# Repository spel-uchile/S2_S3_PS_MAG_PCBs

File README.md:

# S2_S3_PS_MAG_PCBs
A summary of the different MAG derived PCBs used in SUCHAI 2, SUCHAI 3 and Plansat Satellites

## Folder Content

- CADs: CAD files of some PCBs
- Grafeno V2: KiCAD version of Graphene PCB (for debugging)
- mini_sensor: Magnetometer PCB sensor implementation for testing
- PAD: Panel A Cubesat with holes for Langmuir Probe voltage regulator (used as dummy Panel A)
- Panel A E S2: External Panel A Suchai-2. Includes the Magnetometer socket and holes to place the Shielded Langmuir Probe Electronic PCB.
- Panel A E S2 - Plansat: External Panel A Plansat. Includes the Magnetometer socket.
- Panel A E S3: External Panel A Suchai-3. Includes the Magnetometer socket and holes to place the Langmuir Probe Sensor (Not Used).
- Panel A I S2: Internal Panel A Suchai-2. Includes the pines to place the Langmuir Probe voltage Regulator and a hole to introduce the Langmuir Probe PCB Shield beyond the PCB.
- Panel A I S3: Internal Panel A Suchai-3. Includes the pines to place the Langmuir Probe voltage Regulator and a hole to introduce the Langmuir Probe PCB Shield beyond the PCB (Not Used).
- Panel B E S2: External Panel B Suchai-2. Includes the Magnetometer socket and holes to place the Shielded Langmuir Probe Electronic PCB (Not used).
- Panel B E S3: External Panel B Suchai-3. Includes the Magnetometer socket and holes to place the Langmuir Probe Sensor. It also includes a hole for a Particle counter sensor.
- Panel B E S3 - Plansat: External Panel B Plansat. Includes the Magnetometer socket.
- Panel B I S2: Internal Panel B Suchai-2. Includes holes to place the Langmuir Probe Wire (PCB-Sensor) and the Raspberry Pi Camera (Not Used).
- Panel B I S3: Internal Panel B Suchai-3. Includes holes to place the Langmuir Probe Wire (PCB-Sensor), GPS, and the Raspberry Pi Camera.
- Panel B I S3 PC: Internal Panel B Suchai-3. Includes a Particle Counter Circuit Implementation, holes to place the Langmuir Probe Wire (PCB-Sensor), GPS, and the Raspberry Pi Camera.
- Panel Test: PCB to check the achievement of the maximum limits for lateral panels of the Satellite.
- PDB: Dummy Panel B.
- PC: KiCAD version of Particle Counter Prototype Circuit.
- PC104: Magnetometer PCB (MAG) PC104 PCB, Version 1 (Not used).
- PC104 - Plansat: Magnetometer PCB (MAG) PC104 PCB, Plansat Version.
- PC104_V2: Magnetometer PCB (MAG+) PC104 PCB, Version 2 (Used in Suchai-2).
- PC104_V3: Magnetometer PCB (Super MAG+) PC104 PCB, Version 3 (Used in Suchai-3).
- PC104_V3P2: Magnetometer PCB (Super MAG+) PC104 PCB, Version 3 (Added MCP3204 as AOA ADC).
- PC104 main: Compilation of the PC104 and panels used in the project (Version 1).
- PCD: Dummy Panel C.

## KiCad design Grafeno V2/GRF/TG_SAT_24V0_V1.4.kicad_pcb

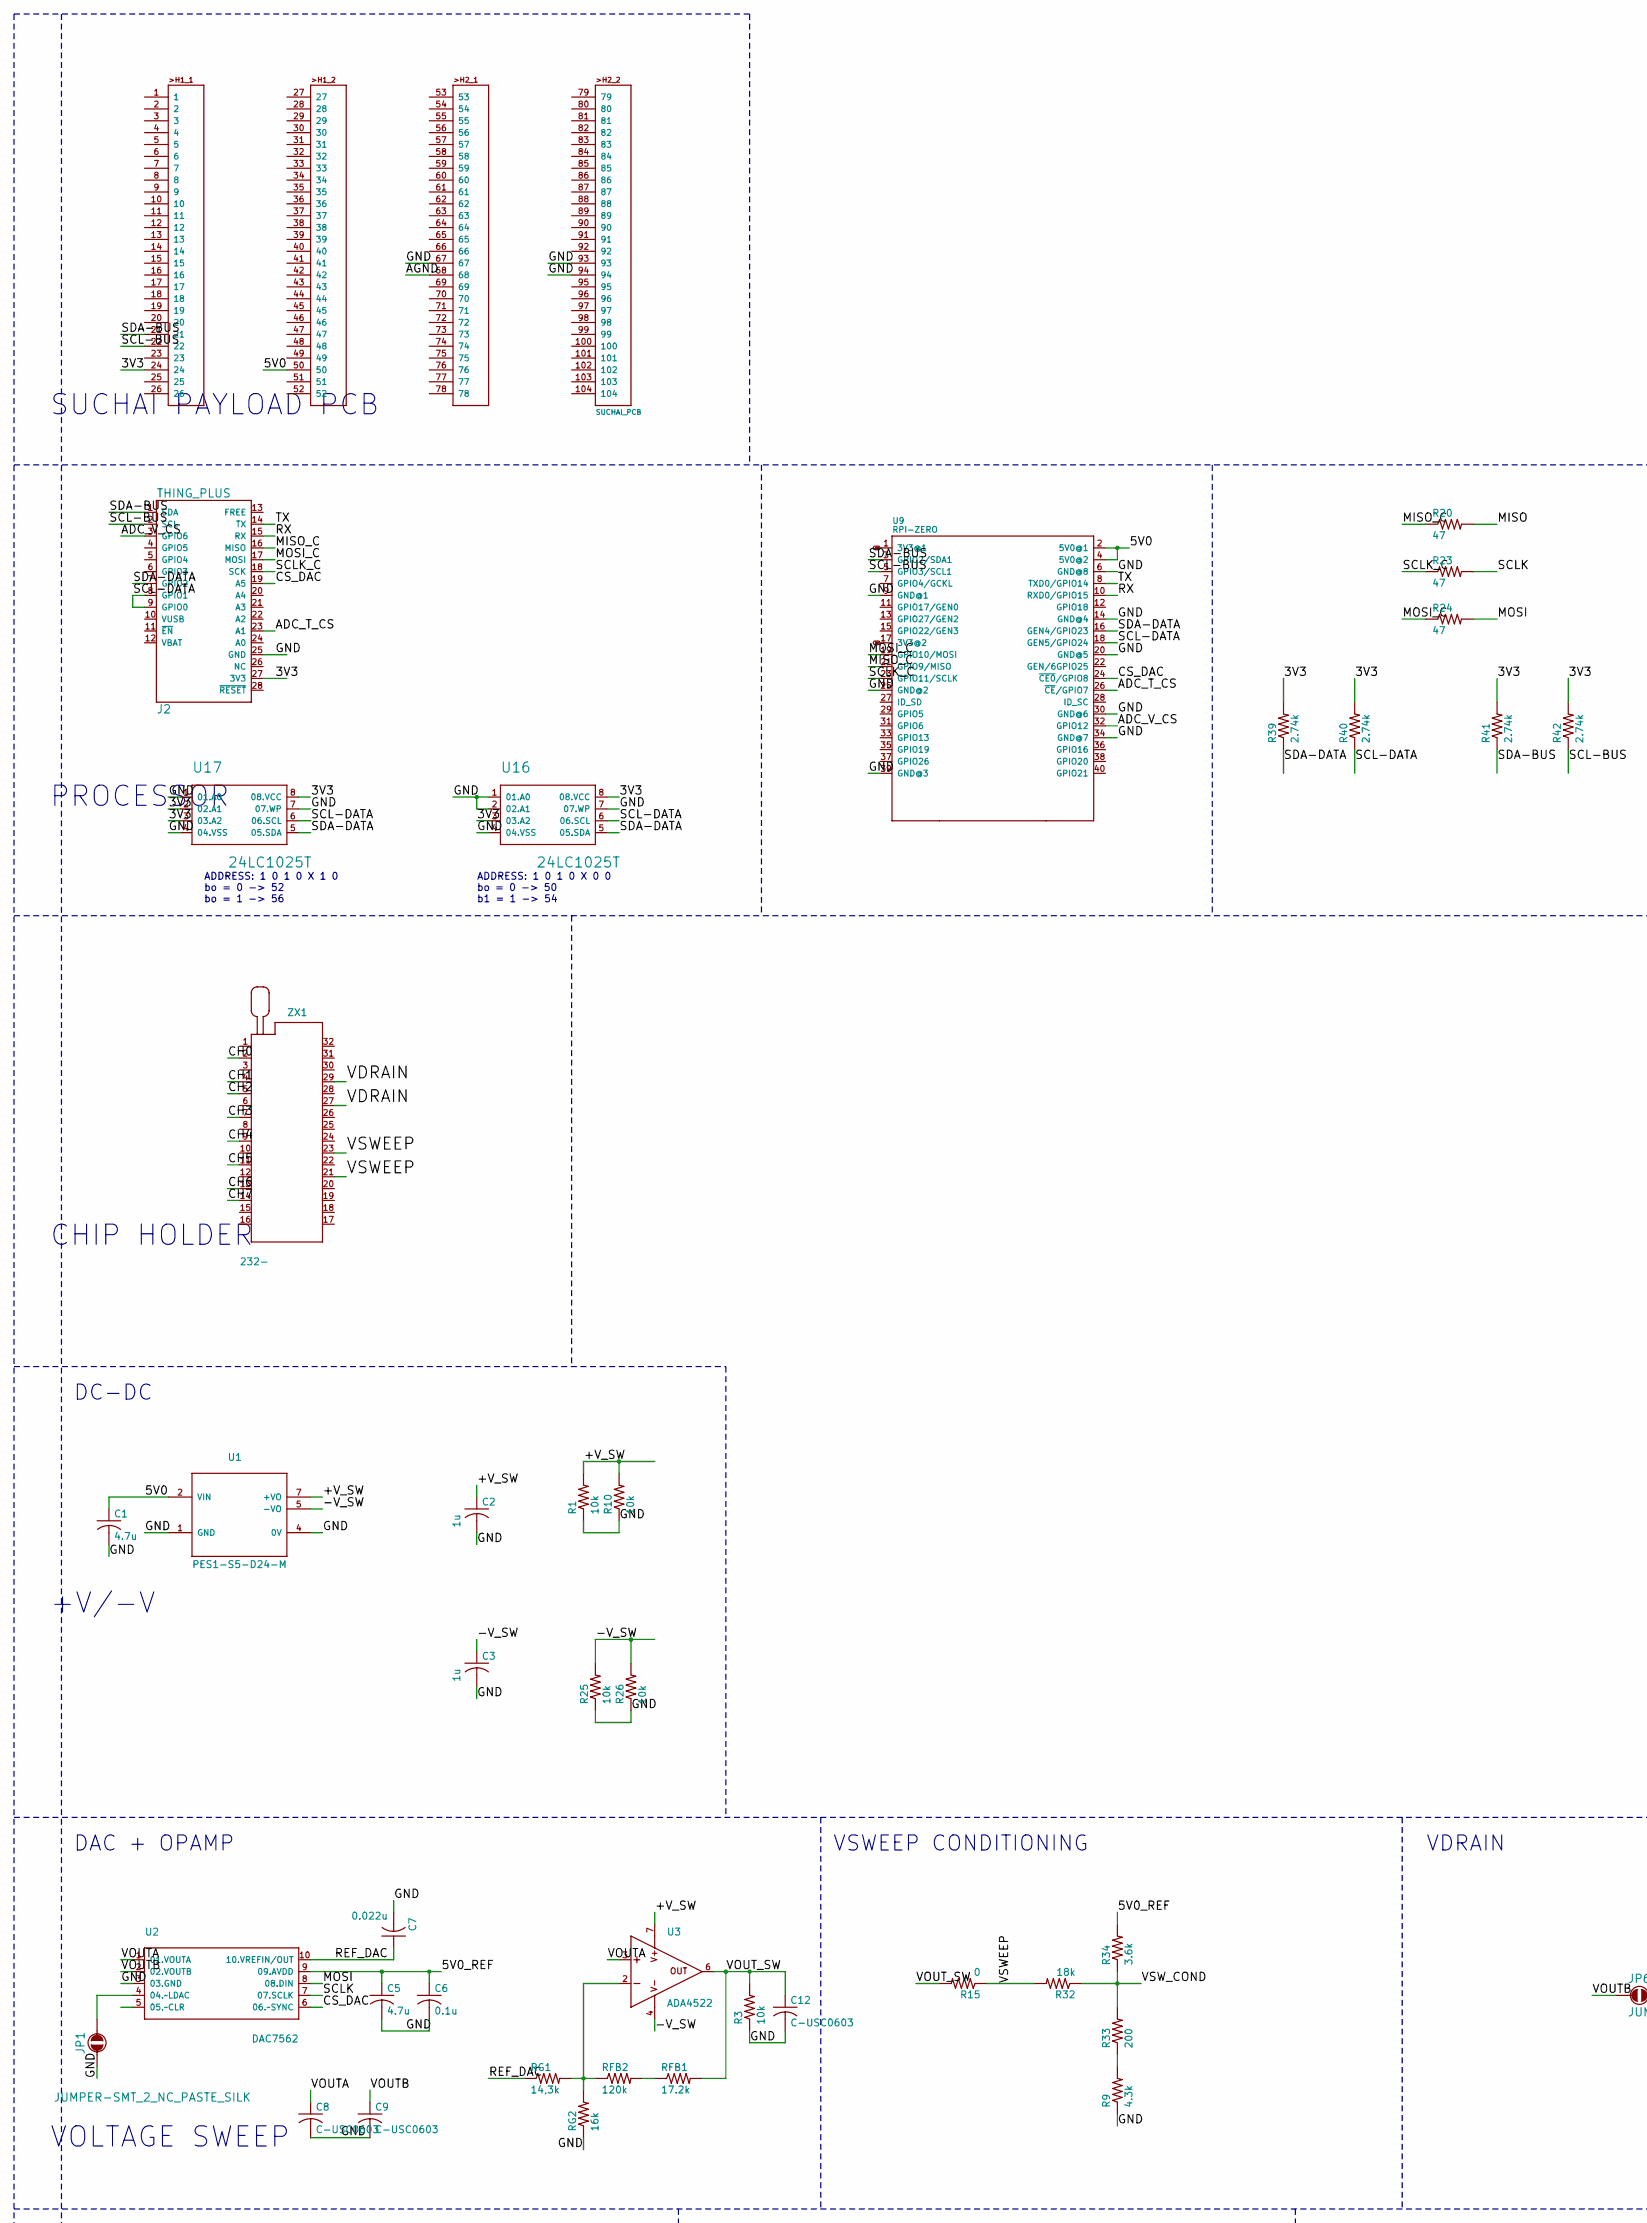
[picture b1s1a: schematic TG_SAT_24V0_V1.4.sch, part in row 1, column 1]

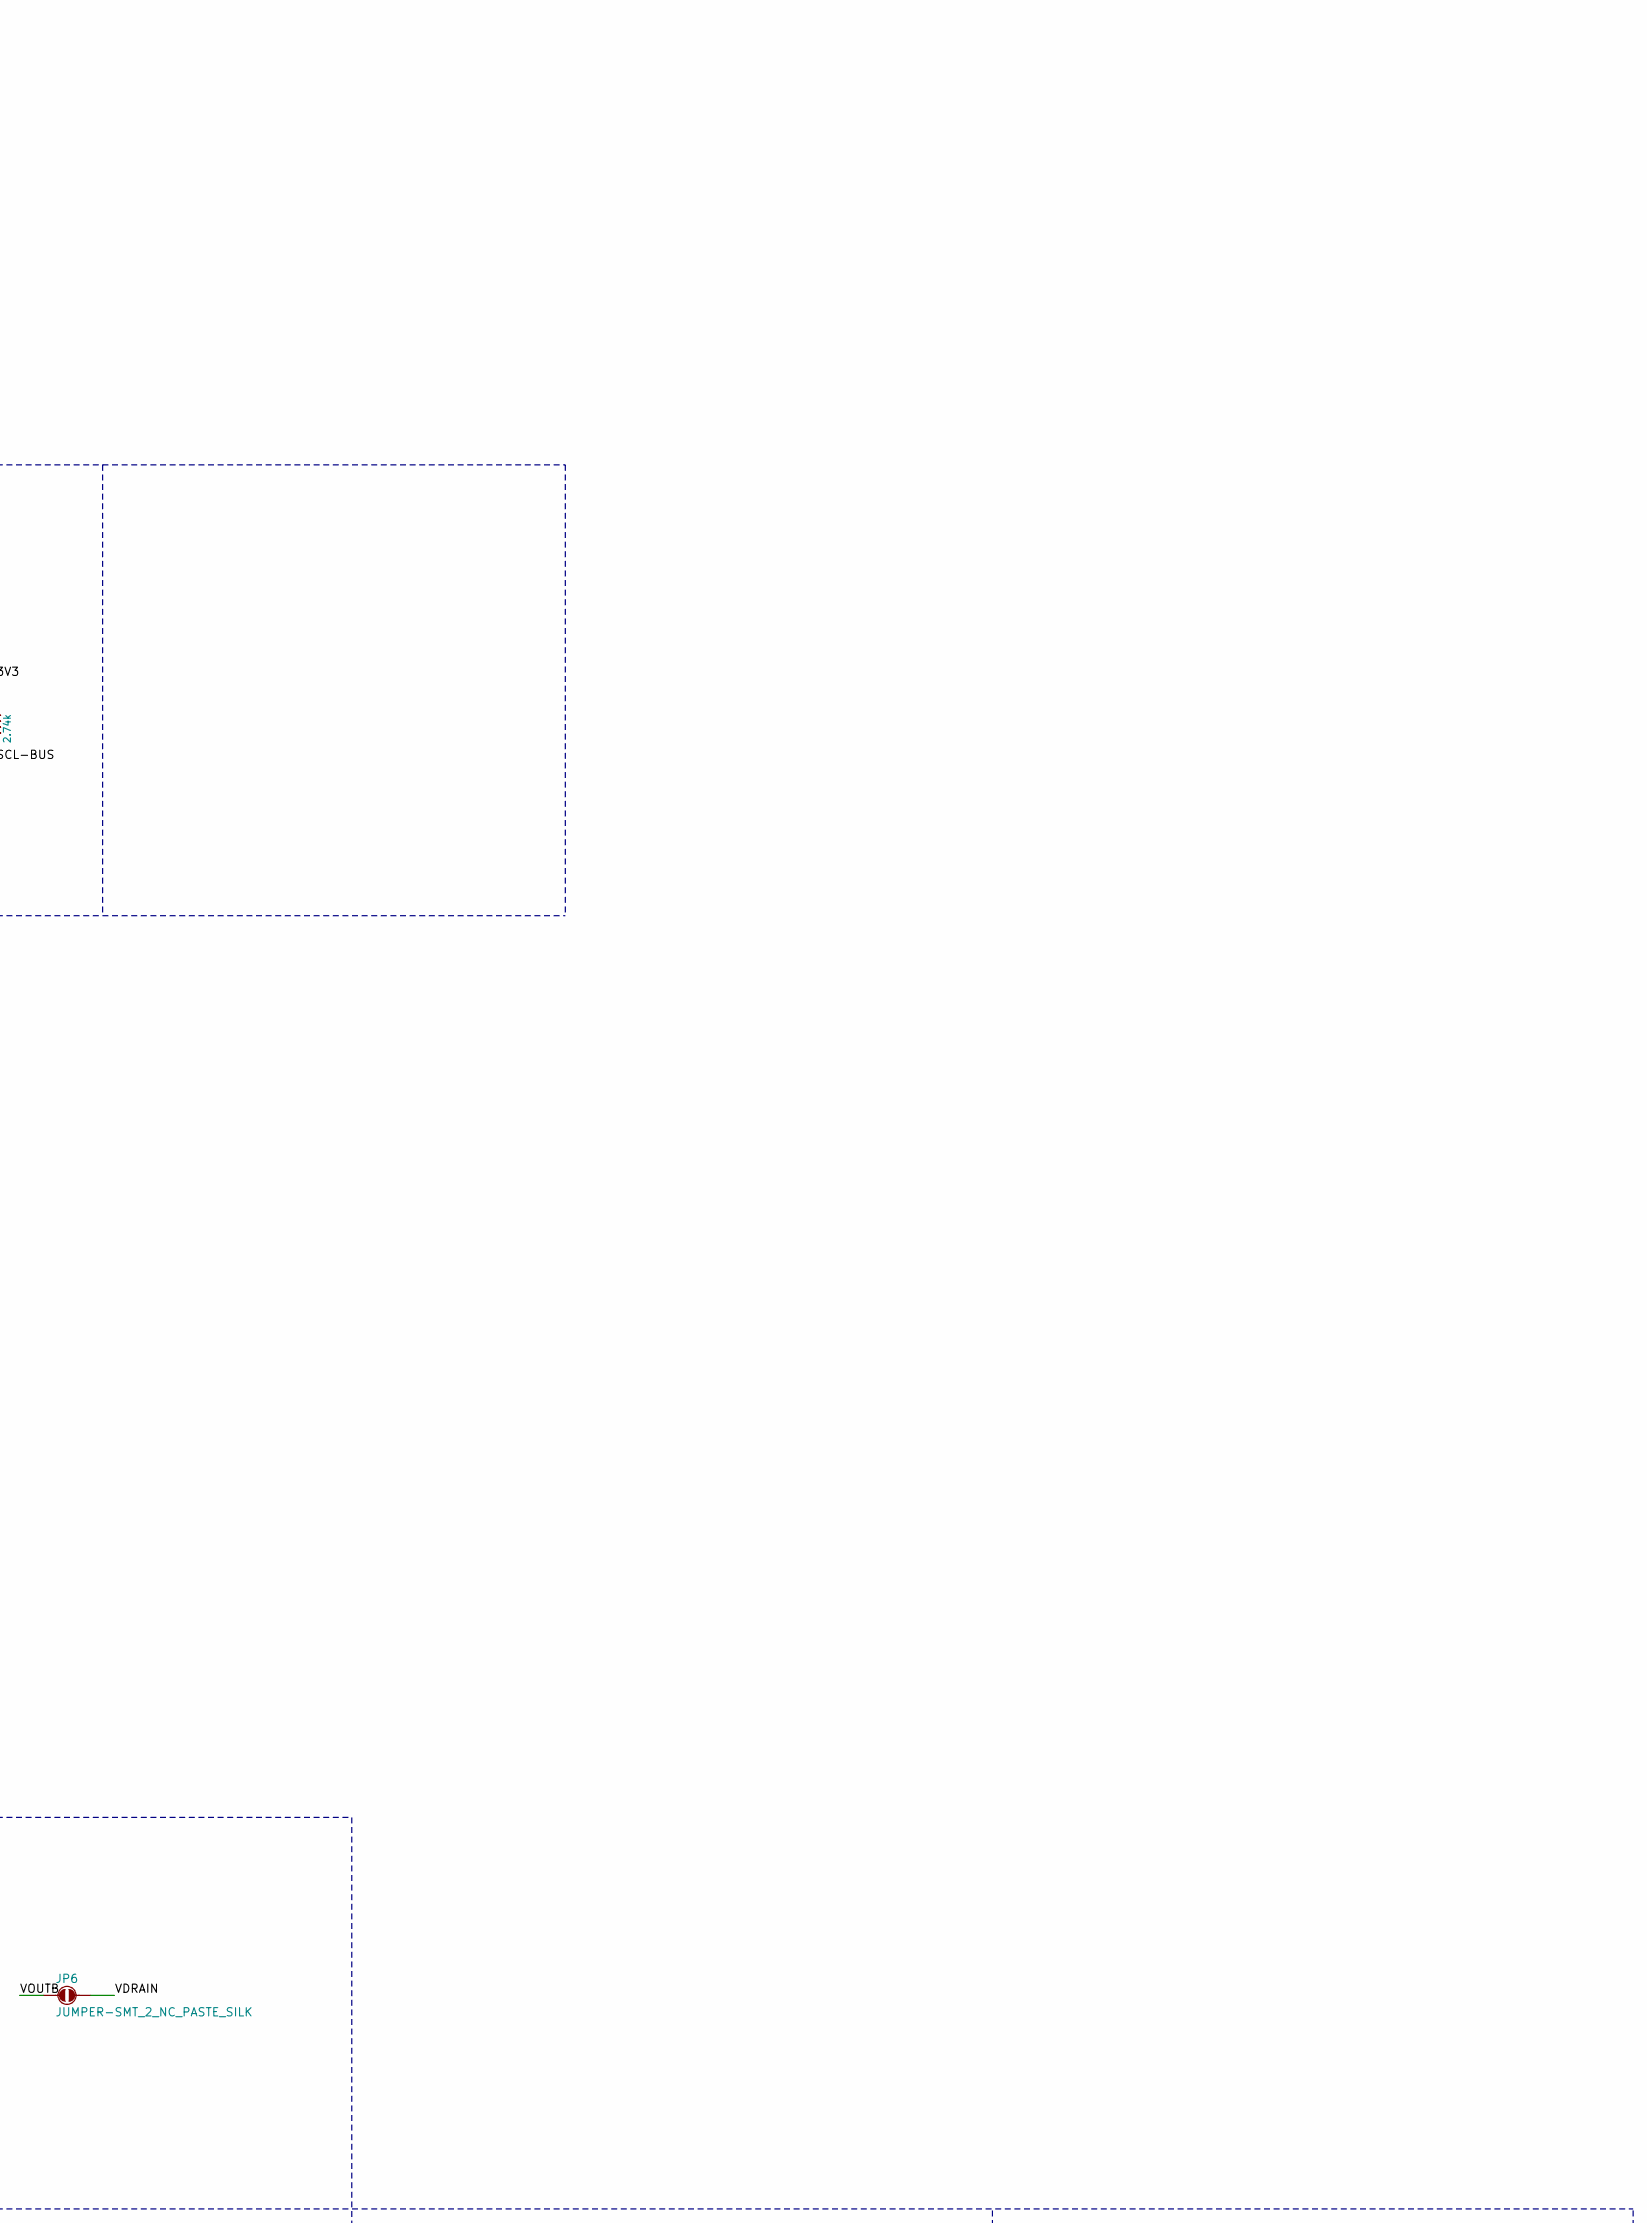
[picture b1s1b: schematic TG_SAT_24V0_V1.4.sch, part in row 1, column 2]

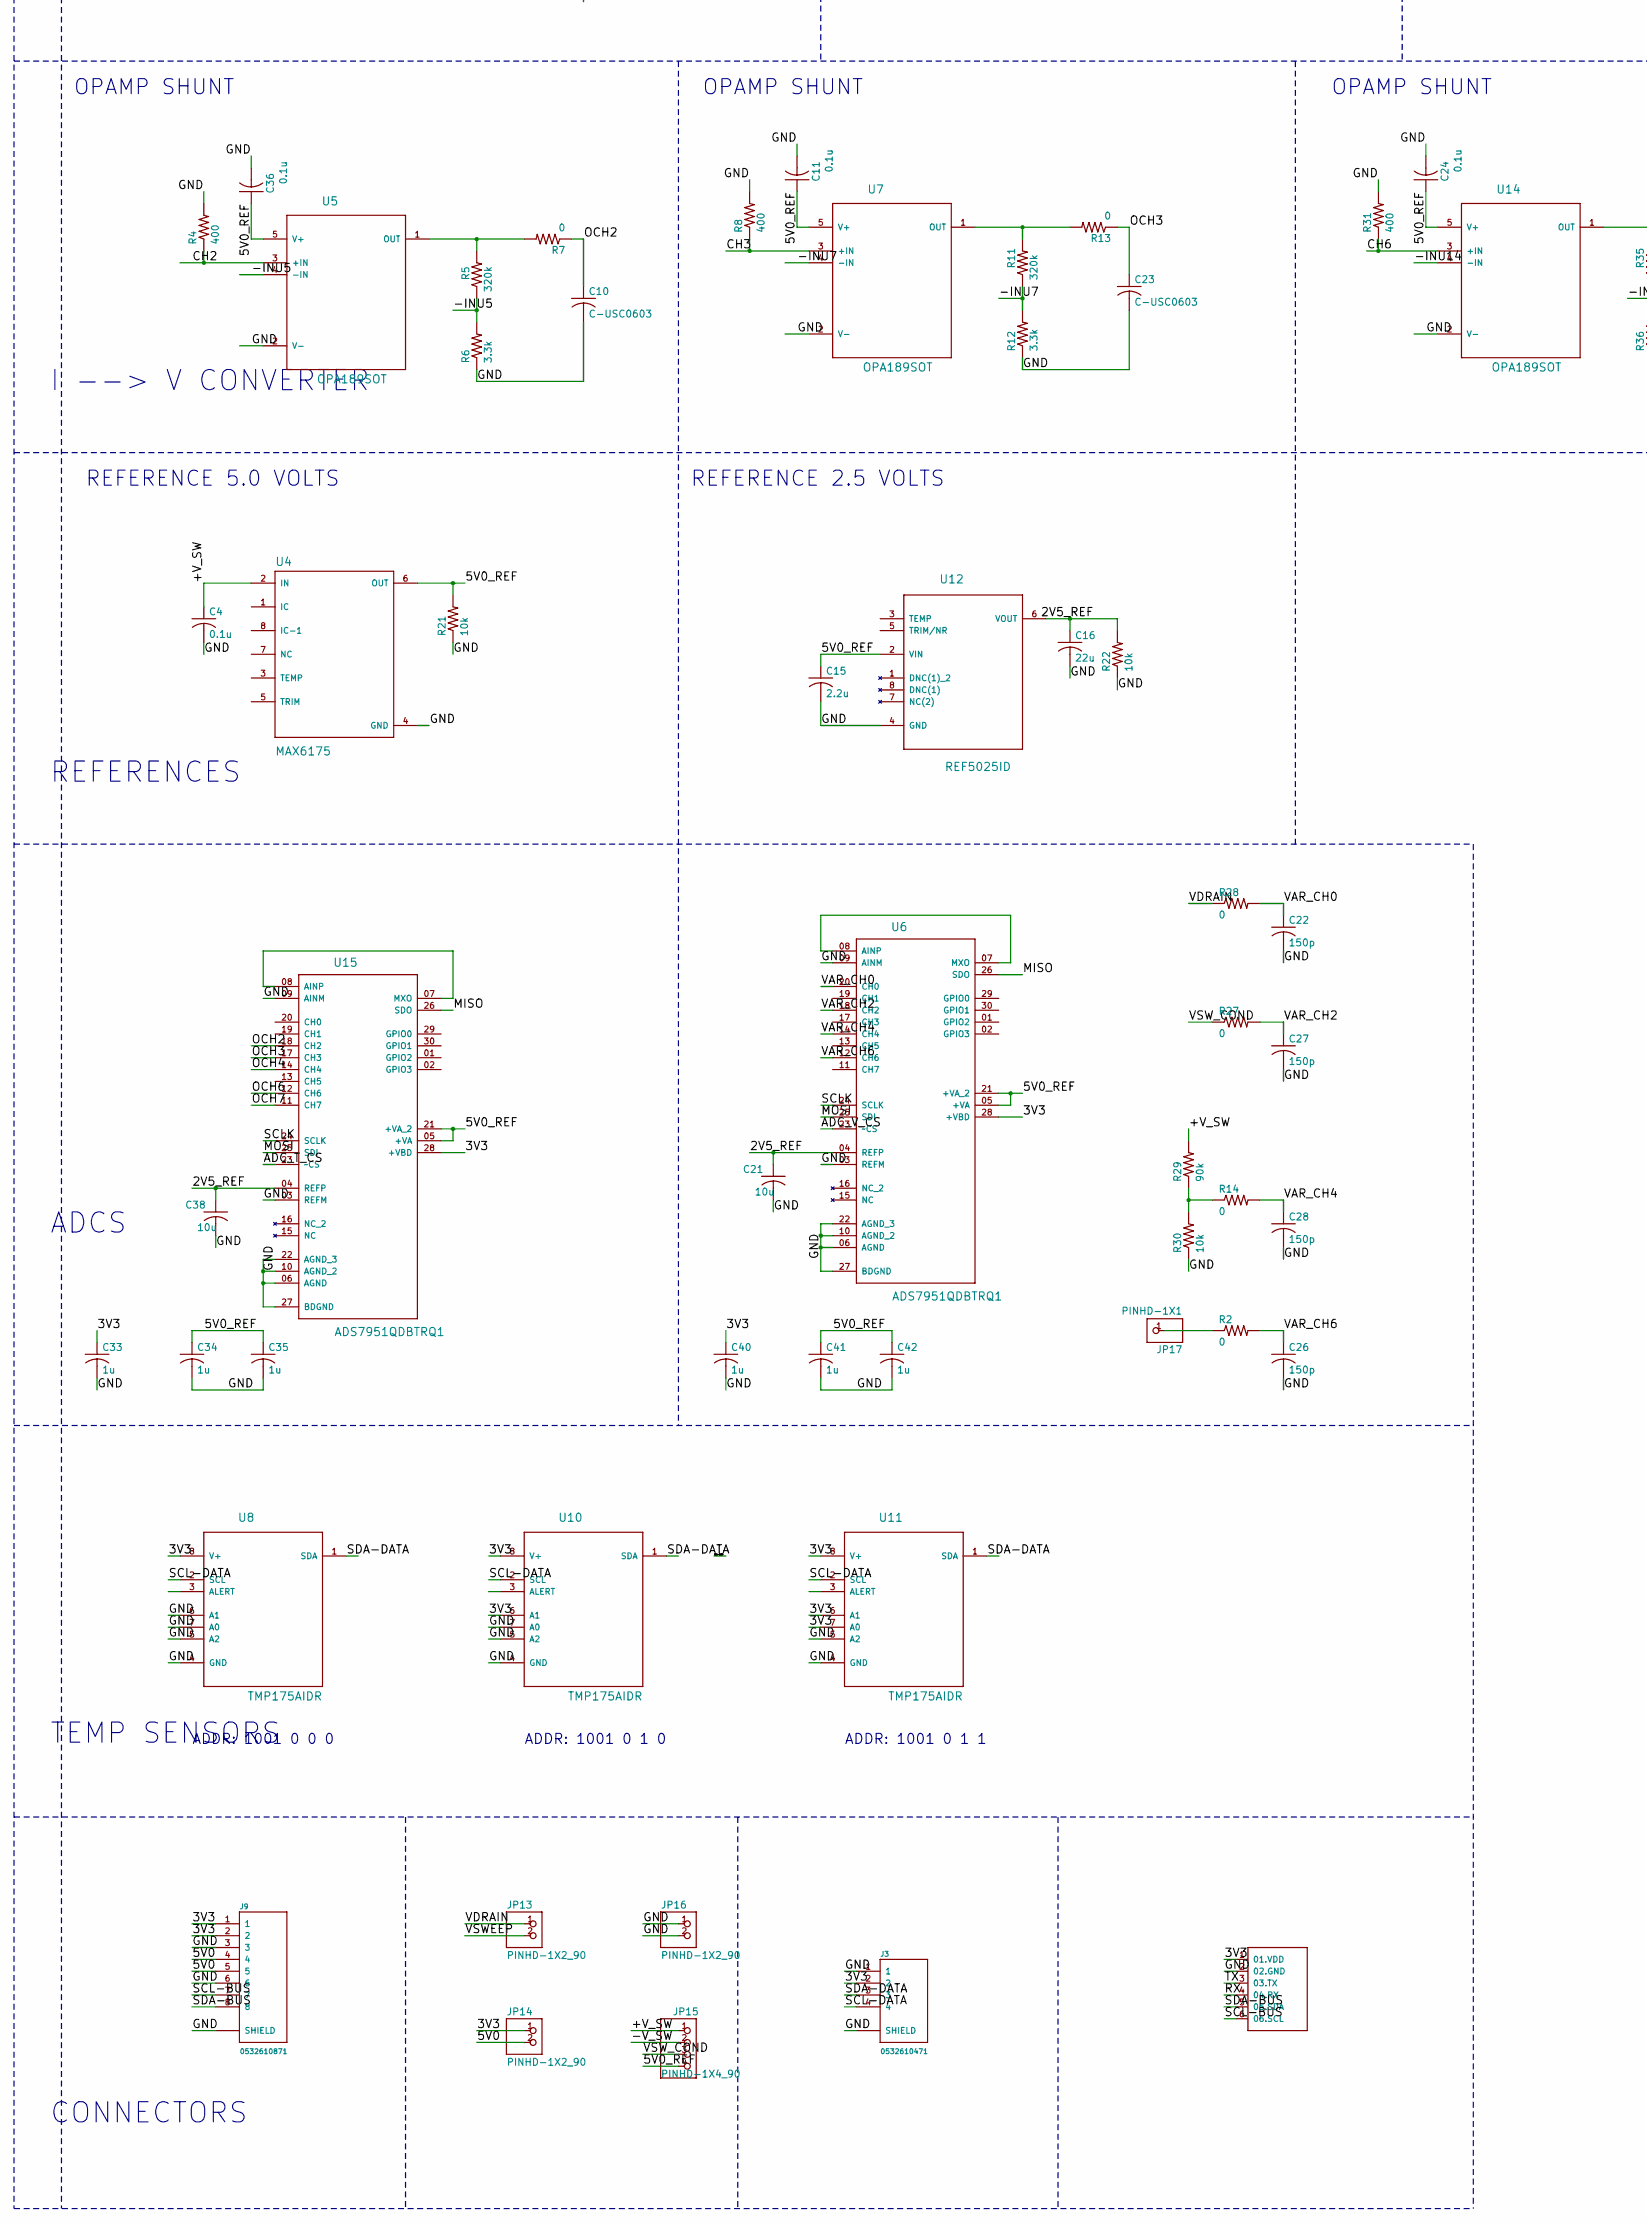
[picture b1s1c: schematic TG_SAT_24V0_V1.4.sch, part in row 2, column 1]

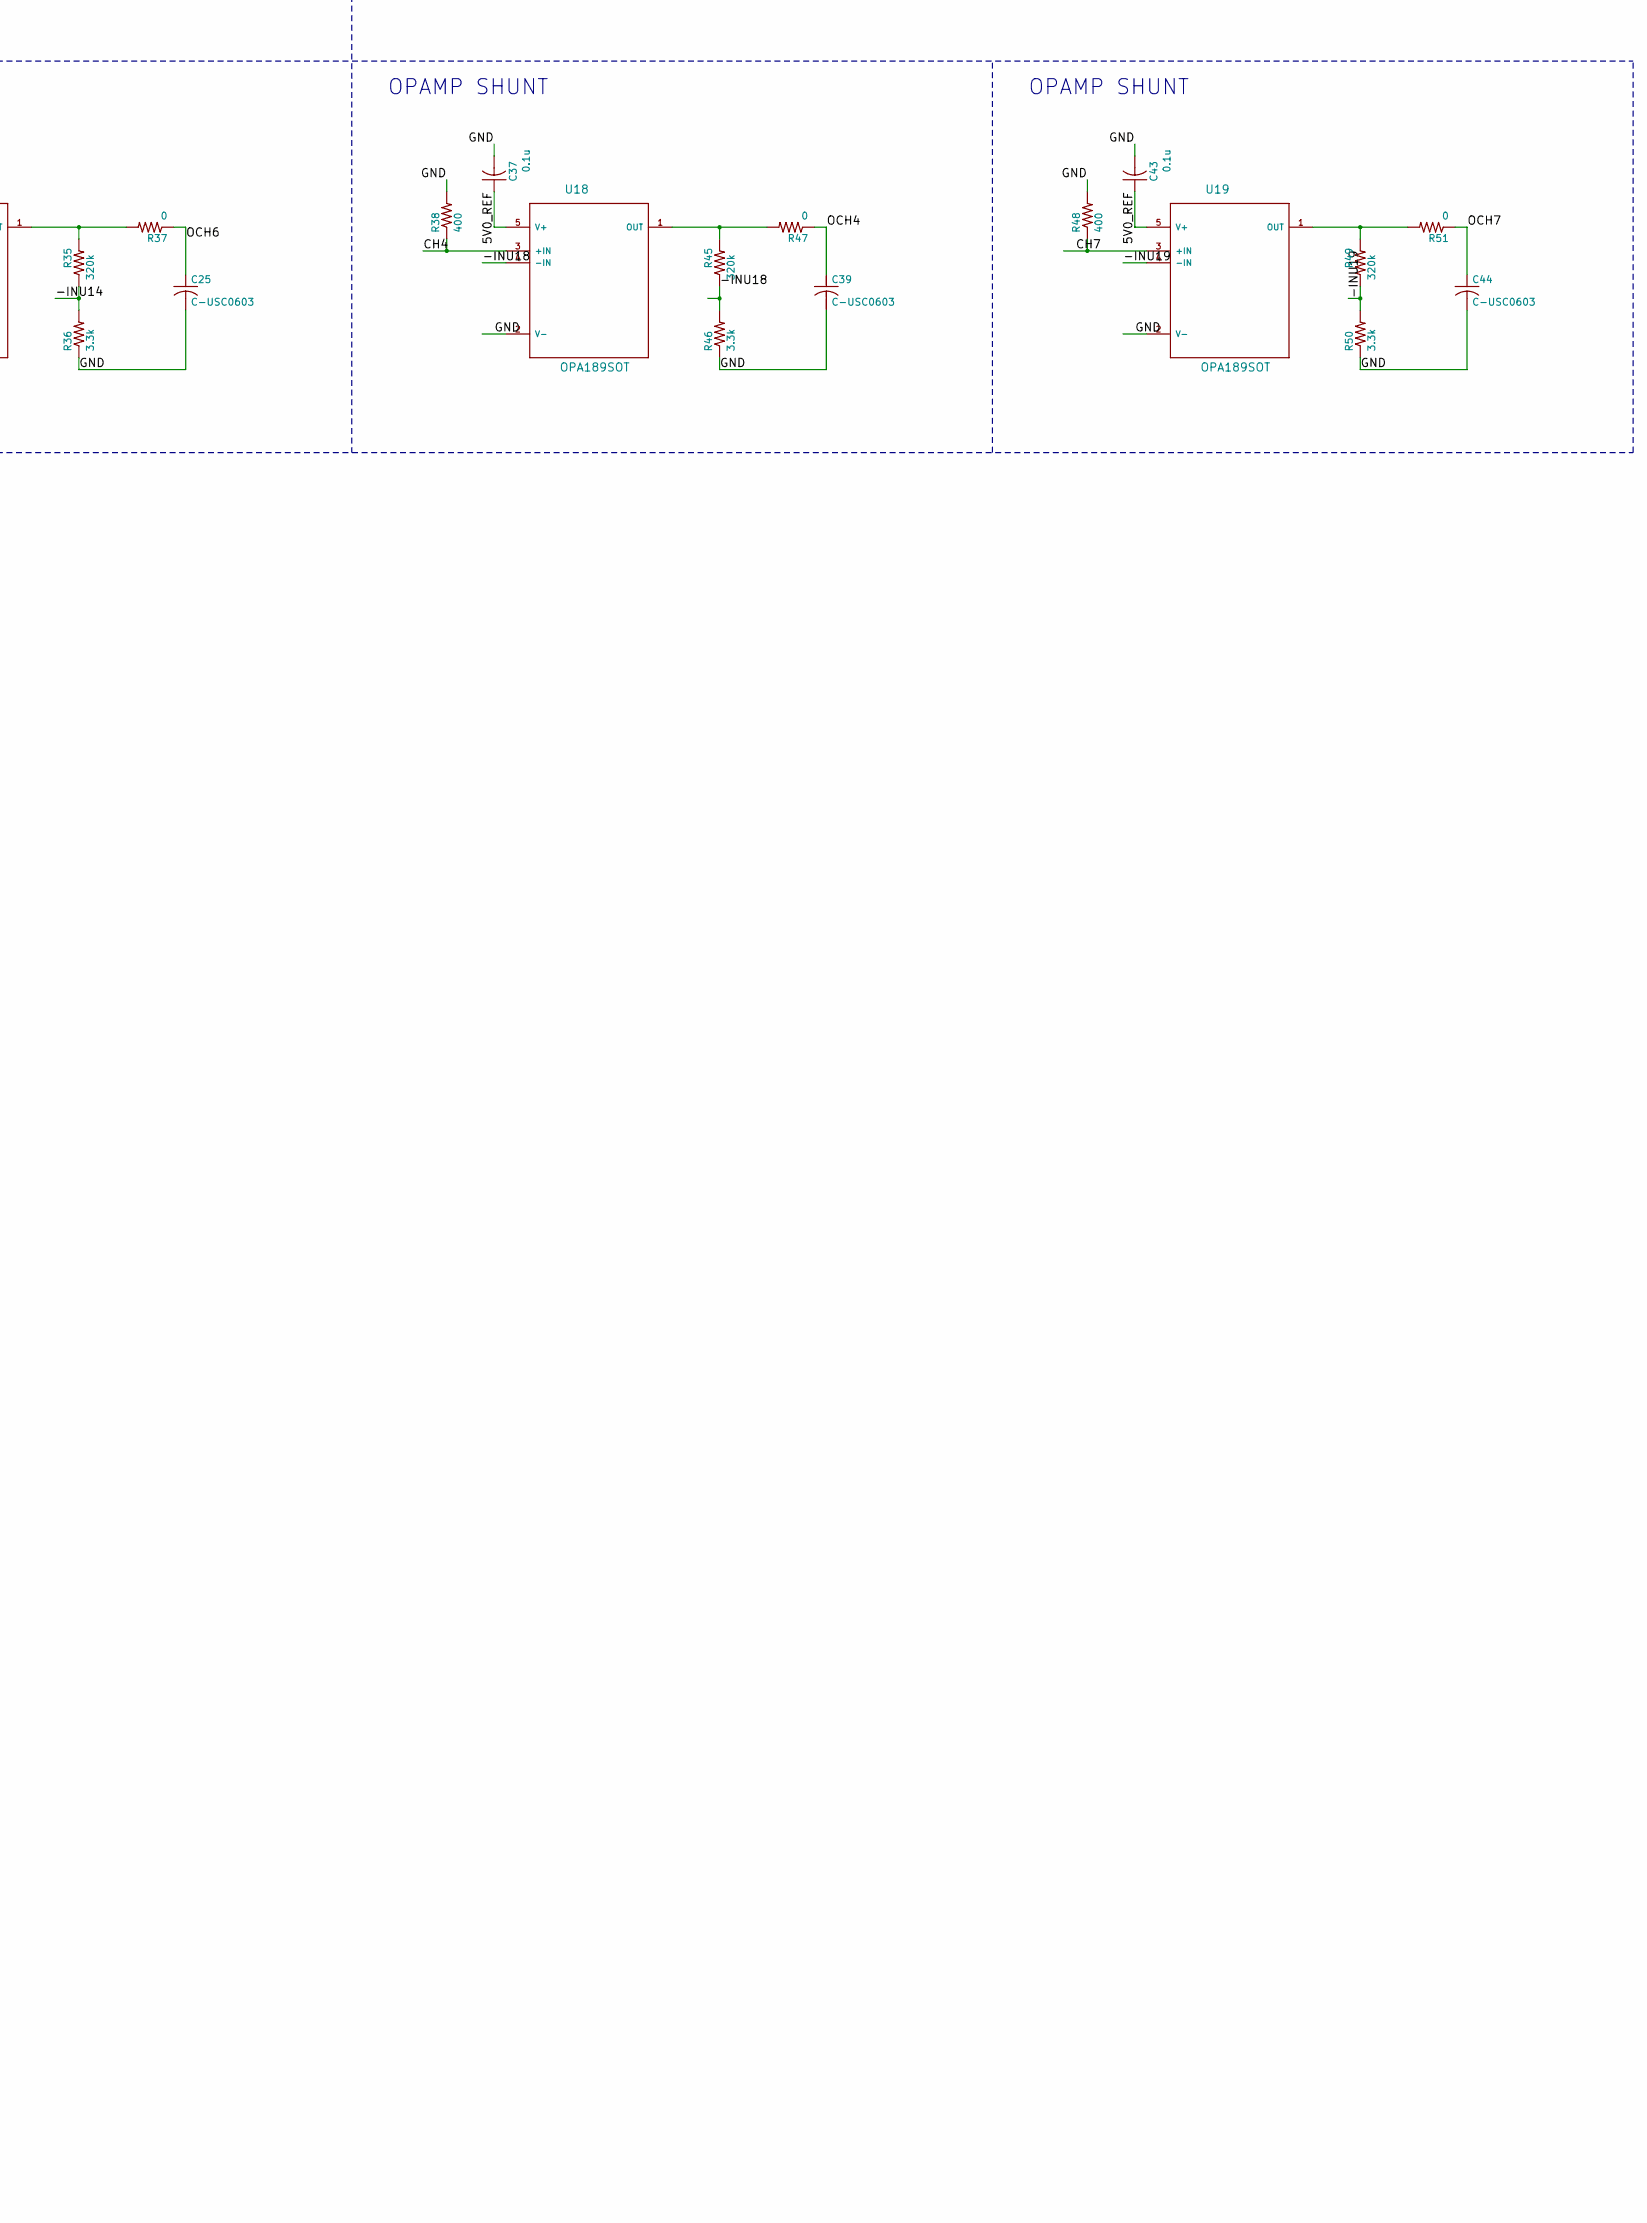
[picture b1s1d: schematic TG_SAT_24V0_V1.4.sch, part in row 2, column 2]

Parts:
C1, C5: 4.7u; C1206
C2, C3, C33, C34, C35, C40, C41, C42: 1u; C0603
C4, C11, C24, C36, C37, C43: 0.1u; C0805
C6: 0.1u; C0603
C7: 0.022u; C0603
C8, C9, C10, C12, C23, C25, C39, C44: C-USC0603; C0603
C15: 2.2u; C1206
C16: 22u; C1206
C21, C38: 10u; C0603
C22, C26, C27, C28: 150p; C0603
J1: SUCHAI_PCB
J2: THING_PLUS
J3: 0532610471; MOLEX_0532610471
J9: 0532610871; MOLEX_0532610871
JP1, JP6: JUMPER-SMT_2_NC_PASTE_SILK; SMT-JUMPER_2_NC_PASTE_SILK
JP13, JP14, JP16: PINHD-1X2_90; 1X02_90
JP15: PINHD-1X4_90; 1X04_90
JP17: PINHD-1X1; 1X01
R1, R3, R10, R21, R22, R25, R26: 10k; R0805
R2, R7, R13, R14, R15, R27, R28, R37, R47, R51: 0; R0603
R4, R8, R31, R38, R48: 400; R0603
R5, R11, R35, R45, R49: 320k; R1206
R6, R12, R36, R46, R50: 3.3k; R0603
R9: 4.3k; R0603
R20, R23, R24: 47; R0603
R29: 90k; R0805
R30: 10k; R0603
R32: 18k; R0603
R33: 200; R0603
R34: 3.6k; R0603
R39, R40, R41, R42: 2.74k; R0603
RFB1: 17.2k; R0603
RFB2: 120k; R0805
RG1: 14,3k; R1206
RG2: 16k; R1206
U1: PES1-S5-D24-M; CONV_PES1-S5-D24-M
U2: DAC7562; SOP50P490X110-10N
U3: ADA4522; SOP65P490X110-8N
U4: MAX6175; SOIC127P600X175-8N
U5, U7, U14, U18, U19: OPA189SOT; SOT95P280X145-5N
U6, U15: ADS7951QDBTRQ1; TSSOP-30
U8, U10, U11: TMP175AIDR; SOIC127P600X175-8N
U9: RPI-ZERO; RASPBERRYPI_BASTELSTUBE_V13_RASPI_BOARD_B+_FULL
U12: REF5025ID; SOIC127P600X175-8N
U16, U17: 24LC1025T; SOIC127P599X173-8N
U$1: BRKOUT-PIC16; BKROUT-PIC16
ZX1: 232-; 3M-MOD

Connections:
3V3: C33.1, C40.1, J1.24, J2.27 (3V3), J3.2, J9.1, J9.2, JP14.1, R39.2, R40.2, R41.2, R42.2, U6.28 (+VBD), U8.8 (V+), U9.1 (3V3@1), U9.17 (3V3@2), U10.6 (A1), U10.8 (V+), U11.6 (A1), U11.7 (A0), U11.8 (V+), U15.28 (+VBD), U16.3 (03.A2), U16.8 (08.VCC), U17.2 (02.A1), U17.3 (03.A2), U17.8 (08.VCC), U$1.1 (01.VDD)
/2V5_REF: C16.1, C21.1, C38.1, R22.2, U6.04 (REFP), U12.6 (VOUT), U15.04 (REFP)
/5V0: C1.1, J1.50, J9.4, J9.5, JP14.2, U1.2 (VIN), U9.2 (5V0@1), U9.4 (5V0@2)
/5V0_REF: C5.1, C6.1, C11.1, C15.1, C24.1, C34.1, C35.1, C36.1, C37.1, C41.1, C42.1, C43.1, JP15.4, R21.2, R34.2, U2.9 (09.AVDD), U4.6 (OUT), U5.5 (V+), U6.05 (+VA), U6.21 (+VA_2), U7.5 (V+), U12.2 (VIN), U14.5 (V+), U15.05 (+VA), U15.21 (+VA_2), U18.5 (V+), U19.5 (V+)
/+V_SW: C2.1, C4.1, JP15.1, R1.2, R10.2, R29.2, U1.7 (+VO), U3.7 (VP), U4.2 (IN)
/-INU5: R5.1, R6.2, U5.4 (-IN)
/-INU7: R11.1, R12.2, U7.4 (-IN)
/-INU14: R35.1, R36.2, U14.4 (-IN)
/-INU18: R45.1, R46.2, U18.4 (-IN)
/-INU19: R49.1, R50.2, U19.4 (-IN)
/-V_SW: C3.1, JP15.2, R25.2, R26.2, U1.5 (-VO), U3.4 (VM)
/ADC_T_CS: J2.23 (A1), U9.26 (~CE~/GPIO7), U15.23 (~~CS)
/ADC_V_CS: J2.3 (GPIO6), U6.23 (~~CS), U9.32 (GPIO12)
/AGND: J1.68
/CH0: ZX1.2
/CH1: ZX1.4
/CH2: R4.1, U5.3 (+IN), ZX1.5
/CH3: R8.1, U7.3 (+IN), ZX1.7
/CH4: R38.1, U18.3 (+IN), ZX1.9
/CH5: ZX1.11
/CH6: R31.1, U14.3 (+IN), ZX1.13
/CH7: R48.1, U19.3 (+IN), ZX1.14
/CS_DAC: J2.19 (A5), U2.6 (06.~~SYNC), U9.24 (~CE0~/GPIO8)
/GND: C1.2, C2.2, C3.2, C4.2, C5.2, C6.2, C7.2, C8.2, C9.2, C10.2, C11.2, C12.2, C15.2, C16.2, C21.2, C22.2, C23.2, C24.2, C25.2, C26.2, C27.2, C28.2, C33.2, C34.2, C35.2, C36.2, C37.2, C38.2, C39.2, C40.2, C41.2, C42.2, C43.2, C44.2, J1.67, J1.93, J1.94, J2.25 (GND), J3.1, J3.S1 (SHIELD), J3.S2 (SHIELD), J9.3, J9.6, J9.S1 (SHIELD), J9.S2 (SHIELD), JP1.1, JP16.1, JP16.2, R1.1, R3.1, R4.2, R6.1, R8.2, R9.1, R10.1, R12.1, R21.1, R22.1, R25.1, R26.1, R30.1, R31.2, R36.1, R38.2, R46.1, R48.2, R50.1, RG2.1, U1.1 (GND), U1.4 (0V), U2.3 (03.GND), U4.4 (GND), U5.2 (V-), U6.03 (REFM), U6.06 (AGND), U6.09 (AINM), U6.10 (AGND_2), U6.22 (AGND_3), U6.27 (BDGND), U7.2 (V-), U8.4 (GND), U8.5 (A2), U8.6 (A1), U8.7 (A0), U9.6 (GND@8), U9.9 (GND@1), U9.14 (GND@4), U9.20 (GND@5), U9.25 (GND@2), U9.30 (GND@6), U9.34 (GND@7), U9.39 (GND@3), U10.4 (GND), U10.5 (A2), U10.7 (A0), U11.4 (GND), U11.5 (A2), U12.4 (GND), U14.2 (V-), U15.03 (REFM), U15.06 (AGND), U15.09 (AINM), U15.10 (AGND_2), U15.22 (AGND_3), U15.27 (BDGND), U16.1 (01.A0), U16.2 (02.A1), U16.4 (04.VSS), U16.7 (07.WP), U17.1 (01.A0), U17.4 (04.VSS), U17.7 (07.WP), U18.2 (V-), U19.2 (V-), U$1.2 (02.GND)
/MISO: R20.2, U6.26 (SDO), U15.26 (SDO)
/MISO_C: J2.16 (MISO), R20.1, U9.21 (GPIO9/MISO)
/MOSI: R24.2, U2.8 (08.DIN), U6.25 (SDI), U15.25 (SDI)
/MOSI_C: J2.17 (MOSI), R24.1, U9.19 (GPIO10/MOSI)
/OCH2: C10.1, R7.1, U15.18 (CH2)
/OCH3: C23.1, R13.1, U15.17 (CH3)
/OCH4: C39.1, R47.1, U15.14 (CH4)
/OCH6: C25.1, R37.1, U15.12 (CH6)
/OCH7: C44.1, R51.1, U15.11 (CH7)
/REF_DAC: C7.1, RG1.1, U2.10 (10.VREFIN/OUT)
/RX: J2.15 (RX), U9.10 (RXD0/GPIO15), U$1.4 (04.RX)
/SCL-BUS: J1.22, J2.2 (SCL), J9.7, R42.1, U9.5 (GPIO3/SCL1), U$1.6 (06.SCL)
/SCL-DATA: J2.8 (GPIO1), J2.9 (GPIO0), J3.4, R40.1, U8.2 (SCL), U9.18 (GEN5/GPIO24), U10.2 (SCL), U11.2 (SCL), U16.6 (06.SCL), U17.6 (06.SCL)
/SCLK: R23.2, U2.7 (07.SCLK), U6.24 (SCLK), U15.24 (SCLK)
/SCLK_C: J2.18 (SCK), R23.1, U9.23 (GPIO11/SCLK)
/SDA-BUS: J1.21, J2.1 (SDA), J9.8, R41.1, U9.3 (GPIO2/SDA1), U$1.5 (05.SDA)
/SDA-DATA: J2.7 (GPIO2), J3.3, R39.1, U8.1 (SDA), U9.16 (GEN4/GPIO23), U10.1 (SDA), U11.1 (SDA), U16.5 (05.SDA), U17.5 (05.SDA)
/TX: J2.14 (TX), U9.8 (TXD0/GPIO14), U$1.3 (03.TX)
/VAR_CH0: C22.1, R28.2, U6.20 (CH0)
/VAR_CH2: C27.1, R27.2, U6.18 (CH2)
/VAR_CH4: C28.1, R14.2, U6.14 (CH4)
/VAR_CH6: C26.1, R2.2, U6.12 (CH6)
/VDRAIN: JP6.2, JP13.1, R28.1, ZX1.27, ZX1.29
/VOUTA: C8.1, U2.1 (01.VOUTA), U3.3
/VOUTB: C9.1, JP6.1, U2.2 (02.VOUTB)
/VOUT_SW: C12.1, R3.2, R15.2, RFB1.2, U3.6 (OUT)
/VSWEEP: JP13.2, R15.1, R32.2, ZX1.21, ZX1.23
/VSW_COND: JP15.3, R27.1, R32.1, R33.2, R34.1
unnamed: JP1.2, U2.4 (04.~~LDAC)
unnamed: JP17.1, R2.1
unnamed: R5.2, R7.2, U5.1 (OUT)
unnamed: R11.2, R13.2, U7.1 (OUT)
unnamed: R14.1, R29.1, R30.2
unnamed: R9.2, R33.1
unnamed: R35.2, R37.2, U14.1 (OUT)
unnamed: R45.2, R47.2, U18.1 (OUT)
unnamed: R49.2, R51.2, U19.1 (OUT)
unnamed: RFB1.1, RFB2.2
unnamed: RFB2.1, RG1.2, RG2.2, U3.2 (M)
unnamed: U6.07 (MXO), U6.08 (AINP)
unnamed: U15.07 (MXO), U15.08 (AINP)

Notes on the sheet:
DC-DC
SUCHAI PAYLOAD PCB
PROCESSOR
CHIP HOLDER
+V/-V
DAC + OPAMP
VOLTAGE SWEEP
OPAMP SHUNT
I --> V CONVERTER
REFERENCE 5.0 VOLTS
REFERENCE 2.5 VOLTS
VSWEEP CONDITIONING
REFERENCES
VDRAIN
ADCS
TEMP SENSORS
ADDR: 1001 0 0 0
ADDR: 1001 0 1 0
ADDR: 1001 0 1 1
CONNECTORS
ADDRESS: 1 0 1 0 X 1 0 bo = 0 -> 52 bo = 1 -> 56
ADDRESS: 1 0 1 0 X 0 0 bo = 0 -> 50 b1 = 1 -> 54

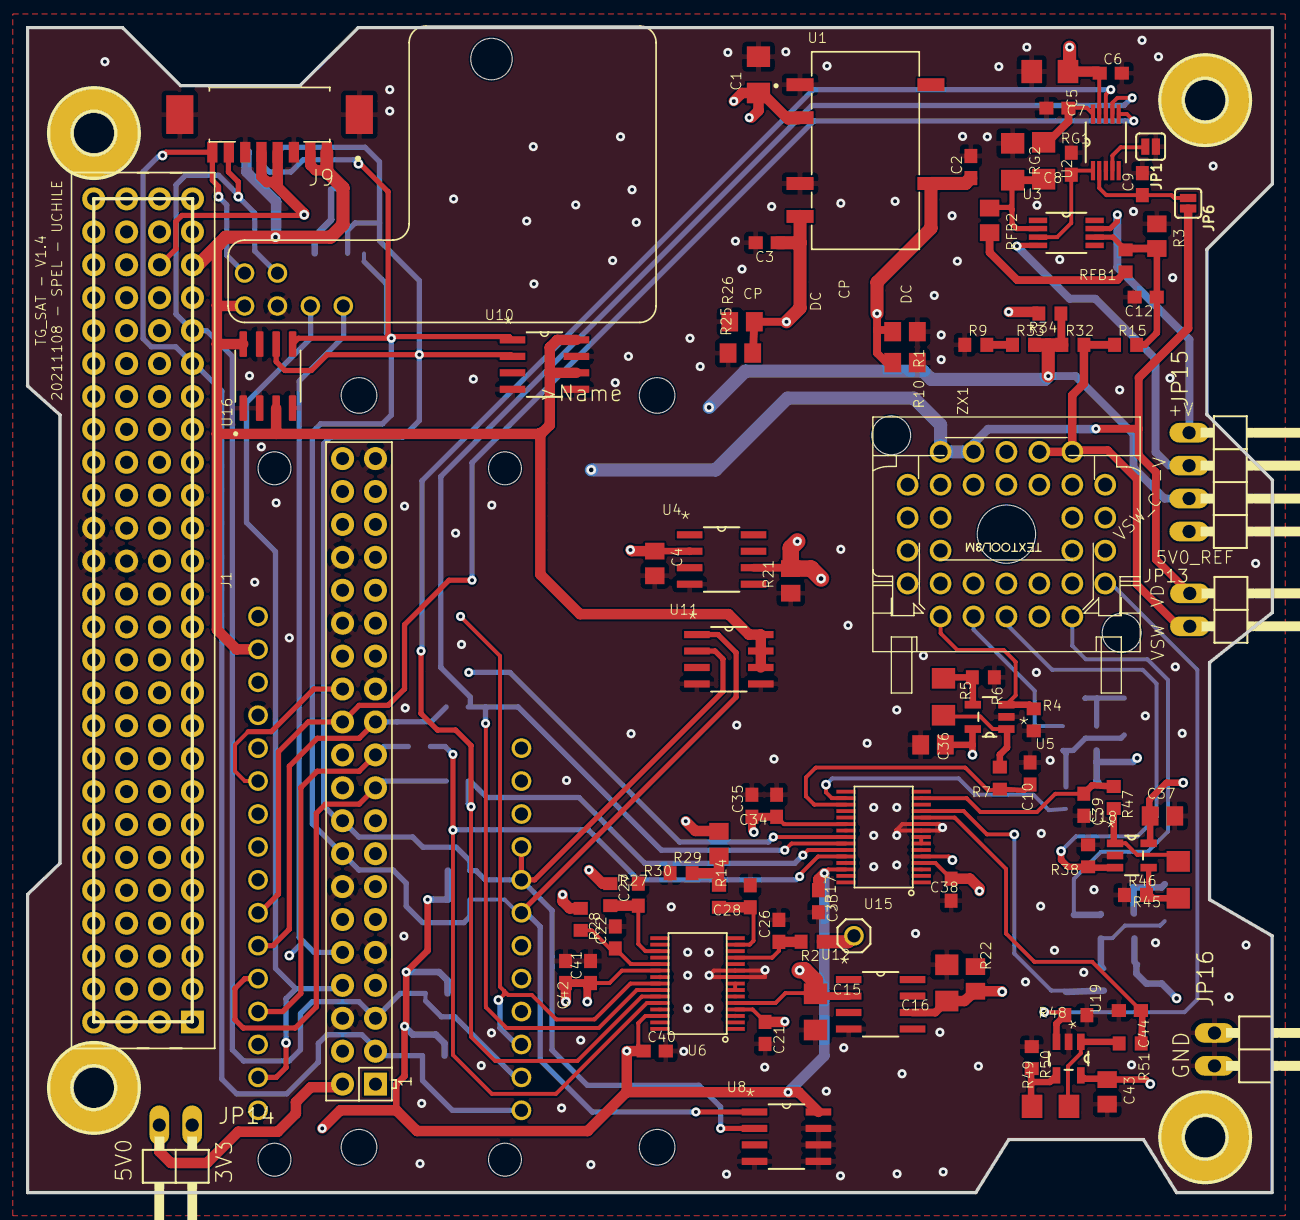
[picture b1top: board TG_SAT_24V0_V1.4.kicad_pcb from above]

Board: 4 copper layers, 96.2 x 90.0 mm, 115 parts (0 on the bottom side), 61 nets.

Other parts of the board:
@HOLE0: (no value)

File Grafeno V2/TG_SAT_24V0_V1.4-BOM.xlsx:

|  |  | TG_DEV-24V0-V1.4 PCS BOM
Item # | *Designator | *Qty | Manufacturer | *Mfg Part # | Description / Value | *Package/Footprint | Type | Your Instructions / Notes
1 | C7 | 1 | Taiyo Yuden | UMF107B7223KAHT | Capacitor, 0,022 uF, +/- 10%, 50V, X7R | 0603 | SMD
2 | C6 | 1 | Yageo | CC0603KRX7R8BB104 | Capacitor, 0,1 uF, +/- 10%, 25V, X7R | 0603 | SMD
3 | J3 | 1 | Molex | 532610841 | Connector 4 ways |  | SMD
4 | J9 | 1 | Molex | 532610871 | Connector 8 ways |  | SMD
5 | R30 | 1 | Yageo | RT0603BRC0710KL | Resistor, 10 kOhm, +/- 0.1%, 0.1W, +/- 15ppm/C° | 0603 | SMD
6 | RFB2 | 1 | Susumu | RG2012N-124-W-T1 | Resistor, 120 kOhm, +/- 0.05%, 0.125W, +/- 10 ppm/C | 0805 | SMD
7 | RG1 | 1 | Panasonic | ERA-8ARW1432V | Resistor, 14,3 kOhm, +/- 0.05%, 0.25W, +/- 10 ppm/C | 1206 | SMD
8 | RG2 | 1 | Panasonic | ERA-8ARW163V | Resistor, 16 kOhm, +/- 0.05%, 0.25W, +/- 10 ppm/C | 1206 | SMD
9 | RFB1 | 1 | KOA Speer | RN73H1JTTD1722B25 | Resistor, 17,2 kOhm, +/- 0.1%, 0.1W, +/-25 ppm/C° | 0603 | SMD
10 | R32 | 1 | Panasonic | ERA-3VRW1802V | Resistor, 18 kOhm, +/-0.05%, 0.1W, +/-10ppm/C° | 0603 | SMD
11 | C15 | 1 | Taiyo Yuden | UMK316B7225MLHT | Capacitor, 2,2 uF, +/-20%, 50V, Low ESR | 1206 | SMD
12 | R33 | 1 | Stackpole | RNCF0603TKY200R | Resistor, 200 Ohm, +/- 0.01%, 0.1W, +/-5 ppm/C° | 0603 | SMD
13 | C16 | 1 | TDK | C3216X5R1V226M160AC | Capacitor, 22 uF, +/- 20%, 35V, X5R | 1206 | SMD
14 | R34 | 1 | Panasonic | ERA-3ARW362V | Resistor, 3,6 kOhm, +/-0.05%, 0.1W, +/-10ppm/C° | 0603 | SMD
15 | R9 | 1 | Panasonic | ERA-3ARW432V | Resistor, 4,3 kOhm, +/- 0.05%, 0.25W, +/- 10 ppm/C | 0603 | SMD
16 | R29 | 1 | Vishay Thin film | PTN0805E9002BST1 | Resistor, 90 kOhm, +/. 0.1%, 0,2W, +/- 25ppm/C° | 0805 | SMD
17 | U3 | 1 | Analog Devices | ADA4522-1ARMZ | Opamp, , Zero-Drift opamp | 8-MSOP | SMD
18 | U2 | 1 | Texas Instruments | DAC7562SDGST | DAC, , 12 bit, 2 channels | 10VSSOP | SMD
19 | U4 | 1 | Maxim Integrated | MAX6175AASA+ | Voltage ref, 5 Volts, 30 mA, ± 0.06%, 3pm/C° | 8-SOIC | SMD
20 | U1 | 1 | CUI Inc | PES1-S5-D24-M-TR | DC-DC Converter, , +24/-24 V, 1W | 8-SMD | SMD
21 | U12 | 1 | Texas Instruments | REF5025IDR | Voltage reference, 2,5 Volts, +/- 0.05%, 10mA, 3 ppm/C° | 8-SOIC | SMD
22 | C21, C38 | 2 | Murata Electronics | GRM188R61E106KA73J | Capacitor, 10 uF, +/- 10%, 25V, X5R | 0603 | SMD
23 | U16, U17 | 2 | Microchip Technology | 24LC1025T-E/SN | EEPROM, 1 Mbit, 1 Mbit, I2C | SOIC-8 | SMD
24 | C1, C5 | 2 | Taiyo Yuden | UMK316ABJ475MLHT | Capacitor, 4,7 uF, +/- 20%, 50V, X5R, Ultra Low ESR | 1206 | SMD
25 | U6, U15 | 2 | Texas Instruments | ADS7951QDBTRQ1 | Analog to Digital Conv, , 12 bit, SAR, 8 input | 30-TSSOP | SMD
26 | R20, R23, R24 | 3 | TE Connectivity | CRGCQ0603J47R | Resistor, 47 Ohm, 5%, 0.1W | 0603 | SMD
27 | U8, U10, U11 | 3 | Texas Instruments | TMP175AQDRQ1 | Temp sensor, , 12 bits | SOIC-8 | SMD
28 | C22, C26, C27, C28 | 4 | Yageo | CC0603FRNPO9BN151 | Capacitor, 150 pF, +/-1%, 50V | 0603 | SMD | DNP/DNI
29 | R39, R40, R41, R42 | 4 | Yageo | RT0603DRD072K74L | Resistor, 2,74 kOhm, +/- 0.5%, 0.1W, +/- 25ppm/C° | 0603 | SMD | DNP/DNI
30 | C8, C9, C12, C10, C23, C25, C39, C44 | 8 | DNP/DNI | DNP/DNI | DNP/DNI | DNP/DNI | DNP/DNI | DNP/DNI
31 | R6, R12, R36, R46, R50 | 5 | Panasonic | ERA-3AEB332V | Resistor, 3,3 kOhm, +/- 0.1%, 0.1W, +/-25ppm/C° | 0603 | SMD
32 | R5, R11, R35, R45, R49 | 5 | KOA Speer | RN732BTTD3203B25 | Resistor, 320 kOhm, +/- 0.1%, 0.125W, +/-25ppm/C° | 1206 | SMD
33 | R4, R8, R31, R38, R48 | 5 | Vishay | PAT0603E4000BST1 | Resistor SHUNT, 400 Ohm, +/- 0.1%, 0.15W, +/-25ppm/C° | 0603 | SMD
34 | U5, U7, U14, U18, U19 | 5 | Texas Instruments | OPA189IDBVR | Opamp, , Zero drift, Rail-to-rail | SOT23-5 | SMD
35 | C4, C11, C24, C36, C37, C43 | 6 | Taiyo Yuden | LMK212SD104KG-T | Capacitor, 0,1 uF, Low ESR, ± 10%, 10V | 0805 | SMD
36 | R1, R3, R10, R21, R22, R25, R26 | 7 | Stackpole | RNCP0805FTD10K0 | Resistor, 10 kOhm, +/- 1%, 0.25W, +/- 100ppm/C° | 0805 | SMD
37 | C2, C3, C33, C34, C35, C40, C41, C42 | 8 | Taiyo Yuden | GMK107BJ105MAHT | Capacitor, 1 uF, +/-20%, 35V, Low ESR | 0603 | SMD
38 | R2, R7, R13, R37, R47, R51, R14, R15, R27, R28 | 10 | Yageo | RC0603JR-070RL | Resistor, 0 Ohm, 1/10 W | 0603 | SMD

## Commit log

2022-08-22 First Commit
    Compilation of the different PCBs developed for the MAG subsystem for the SUCHAI-2, SUCHAI-3 and Plantsat Satellites.

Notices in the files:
parts and their libraries:
SparkFun-Jumpers: Licensing: Creative Commons ShareAlike 4.0 International - https://creativecommons.org/licenses/by-sa/4.0
